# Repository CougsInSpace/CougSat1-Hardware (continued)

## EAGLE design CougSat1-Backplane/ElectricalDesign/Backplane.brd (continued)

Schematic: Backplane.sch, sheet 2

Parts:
J0, J1, J2, J3: CougSat Socket; PCIE-8

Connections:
BUS_I2C0_IRQ: J0.A45 (BUS_I2C0_IRQ), J0.B45 (BUS_I2C0_IRQ), J1.A45 (BUS_I2C0_IRQ), J1.B45 (BUS_I2C0_IRQ), J2.A45 (BUS_I2C0_IRQ), J2.B45 (BUS_I2C0_IRQ), J3.A45 (BUS_I2C0_IRQ), J3.B45 (BUS_I2C0_IRQ); also elsewhere on the board
BUS_I2C0_SCL: J0.A44 (BUS_I2C0_SCL), J0.B44 (BUS_I2C0_SCL), J1.A44 (BUS_I2C0_SCL), J1.B44 (BUS_I2C0_SCL), J2.A44 (BUS_I2C0_SCL), J2.B44 (BUS_I2C0_SCL), J3.A44 (BUS_I2C0_SCL), J3.B44 (BUS_I2C0_SCL); also elsewhere on the board
BUS_I2C0_SDA: J0.A43 (BUS_I2C0_SDA), J0.B43 (BUS_I2C0_SDA), J1.A43 (BUS_I2C0_SDA), J1.B43 (BUS_I2C0_SDA), J2.A43 (BUS_I2C0_SDA), J2.B43 (BUS_I2C0_SDA), J3.A43 (BUS_I2C0_SDA), J3.B43 (BUS_I2C0_SDA); also elsewhere on the board
BUS_I2C1_IRQ: J0.A32 (BUS_I2C1_IRQ), J0.B32 (BUS_I2C1_IRQ), J1.A32 (BUS_I2C1_IRQ), J1.B32 (BUS_I2C1_IRQ), J2.A32 (BUS_I2C1_IRQ), J2.B32 (BUS_I2C1_IRQ), J3.A32 (BUS_I2C1_IRQ), J3.B32 (BUS_I2C1_IRQ); also elsewhere on the board
BUS_I2C1_SCL: J0.A31 (BUS_I2C1_SCL), J0.B31 (BUS_I2C1_SCL), J1.A31 (BUS_I2C1_SCL), J1.B31 (BUS_I2C1_SCL), J2.A31 (BUS_I2C1_SCL), J2.B31 (BUS_I2C1_SCL), J3.A31 (BUS_I2C1_SCL), J3.B31 (BUS_I2C1_SCL); also elsewhere on the board
BUS_I2C1_SDA: J0.A30 (BUS_I2C1_SDA), J0.B30 (BUS_I2C1_SDA), J1.A30 (BUS_I2C1_SDA), J1.B30 (BUS_I2C1_SDA), J2.A30 (BUS_I2C1_SDA), J2.B30 (BUS_I2C1_SDA), J3.A30 (BUS_I2C1_SDA), J3.B30 (BUS_I2C1_SDA); also elsewhere on the board
BUS_JTAG_EN-0: J0.B46 (BUS_JTAG_EN-0), J1.B46 (BUS_JTAG_EN-0), J2.B46 (BUS_JTAG_EN-0), J3.B46 (BUS_JTAG_EN-0); also elsewhere on the board
BUS_JTAG_EN-1: J0.B47 (BUS_JTAG_EN-1), J1.B47 (BUS_JTAG_EN-1), J2.B47 (BUS_JTAG_EN-1), J3.B47 (BUS_JTAG_EN-1); also elsewhere on the board
BUS_JTAG_EN-2: J0.B48 (BUS_JTAG_EN-2), J1.B48 (BUS_JTAG_EN-2), J2.B48 (BUS_JTAG_EN-2), J3.B48 (BUS_JTAG_EN-2); also elsewhere on the board
BUS_JTAG_EN-3: J0.B49 (BUS_JTAG_EN-3), J1.B49 (BUS_JTAG_EN-3), J2.B49 (BUS_JTAG_EN-3), J3.B49 (BUS_JTAG_EN-3); also elsewhere on the board
BUS_JTAG_TCK: J0.A46 (BUS_JTAG_TCK), J1.A46 (BUS_JTAG_TCK), J2.A46 (BUS_JTAG_TCK), J3.A46 (BUS_JTAG_TCK); also elsewhere on the board
BUS_JTAG_TDI: J0.A47 (BUS_JTAG_TDI), J1.A47 (BUS_JTAG_TDI), J2.A47 (BUS_JTAG_TDI), J3.A47 (BUS_JTAG_TDI); also elsewhere on the board
BUS_JTAG_TDO: J0.A48 (BUS_JTAG_TDO), J1.A48 (BUS_JTAG_TDO), J2.A48 (BUS_JTAG_TDO), J3.A48 (BUS_JTAG_TDO); also elsewhere on the board
BUS_JTAG_TMS: J0.A49 (BUS_JTAG_TMS), J1.A49 (BUS_JTAG_TMS), J2.A49 (BUS_JTAG_TMS), J3.A49 (BUS_JTAG_TMS); also elsewhere on the board
BUS_SPI_MISO: J0.A38 (BUS_SPI_MISO), J0.B38 (BUS_SPI_MISO), J1.A38 (BUS_SPI_MISO), J1.B38 (BUS_SPI_MISO), J2.A38 (BUS_SPI_MISO), J2.B38 (BUS_SPI_MISO), J3.A38 (BUS_SPI_MISO), J3.B38 (BUS_SPI_MISO); also elsewhere on the board
BUS_SPI_MOSI: J0.A39 (BUS_SPI_MOSI), J0.B39 (BUS_SPI_MOSI), J1.A39 (BUS_SPI_MOSI), J1.B39 (BUS_SPI_MOSI), J2.A39 (BUS_SPI_MOSI), J2.B39 (BUS_SPI_MOSI), J3.A39 (BUS_SPI_MOSI), J3.B39 (BUS_SPI_MOSI); also elsewhere on the board
BUS_SPI_SCK: J0.A37 (BUS_SPI_SCK), J0.B37 (BUS_SPI_SCK), J1.A37 (BUS_SPI_SCK), J1.B37 (BUS_SPI_SCK), J2.A37 (BUS_SPI_SCK), J2.B37 (BUS_SPI_SCK), J3.A37 (BUS_SPI_SCK), J3.B37 (BUS_SPI_SCK); also elsewhere on the board
COM_SPI_CS: J0.A36 (COM_SPI_CS), J0.B36 (COM_SPI_CS), J1.A36 (COM_SPI_CS), J1.B36 (COM_SPI_CS), J2.A36 (COM_SPI_CS), J2.B36 (COM_SPI_CS), J3.A36 (COM_SPI_CS), J3.B36 (COM_SPI_CS); also elsewhere on the board
COM_SPI_MISO: J0.A34 (COM_SPI_MISO), J0.B34 (COM_SPI_MISO), J1.A34 (COM_SPI_MISO), J1.B34 (COM_SPI_MISO), J2.A34 (COM_SPI_MISO), J2.B34 (COM_SPI_MISO), J3.A34 (COM_SPI_MISO), J3.B34 (COM_SPI_MISO); also elsewhere on the board
COM_SPI_MOSI: J0.A35 (COM_SPI_MOSI), J0.B35 (COM_SPI_MOSI), J1.A35 (COM_SPI_MOSI), J1.B35 (COM_SPI_MOSI), J2.A35 (COM_SPI_MOSI), J2.B35 (COM_SPI_MOSI), J3.A35 (COM_SPI_MOSI), J3.B35 (COM_SPI_MOSI); also elsewhere on the board
COM_SPI_SCK: J0.A33 (COM_SPI_SCK), J0.B33 (COM_SPI_SCK), J1.A33 (COM_SPI_SCK), J1.B33 (COM_SPI_SCK), J2.A33 (COM_SPI_SCK), J2.B33 (COM_SPI_SCK), J3.A33 (COM_SPI_SCK), J3.B33 (COM_SPI_SCK); also elsewhere on the board
CTRL_SYNC: J0.A42 (CTRL_SYNC), J0.B42 (CTRL_SYNC), J1.A42 (CTRL_SYNC), J1.B42 (CTRL_SYNC), J2.A42 (CTRL_SYNC), J2.B42 (CTRL_SYNC), J3.A42 (CTRL_SYNC), J3.B42 (CTRL_SYNC); also elsewhere on the board
GPIO-0: J0.A24 (GPIO-0), J1.A24 (GPIO-0), J2.A24 (GPIO-0), J3.A24 (GPIO-0); also elsewhere on the board
GPIO-1: J0.A25 (GPIO-1), J1.A25 (GPIO-1), J2.A25 (GPIO-1), J3.A25 (GPIO-1); also elsewhere on the board
GPIO-2: J0.A26 (GPIO-2), J1.A26 (GPIO-2), J2.A26 (GPIO-2), J3.A26 (GPIO-2); also elsewhere on the board
GPIO-3: J0.A27 (GPIO-3), J1.A27 (GPIO-3), J2.A27 (GPIO-3), J3.A27 (GPIO-3); also elsewhere on the board
GPIO-4: J0.A28 (GPIO-4), J1.A28 (GPIO-4), J2.A28 (GPIO-4), J3.A28 (GPIO-4); also elsewhere on the board
GPIO-5: J0.A29 (GPIO-5), J1.A29 (GPIO-5), J2.A29 (GPIO-5), J3.A29 (GPIO-5); also elsewhere on the board
GPIO-6: J0.A41 (GPIO-6), J1.A41 (GPIO-6), J2.A41 (GPIO-6), J3.A41 (GPIO-6); also elsewhere on the board
GPIO-7: J0.B41 (GPIO-7), J1.B41 (GPIO-7), J2.B41 (GPIO-7), J3.B41 (GPIO-7); also elsewhere on the board

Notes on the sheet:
<3A4>
<3B4>
<3C4>

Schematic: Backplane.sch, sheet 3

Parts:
J4: CougSat Socket; PCIE-8

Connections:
BUS_I2C0_IRQ: J4.A45 (BUS_I2C0_IRQ), J4.B45 (BUS_I2C0_IRQ); also elsewhere on the board
BUS_I2C0_SCL: J4.A44 (BUS_I2C0_SCL), J4.B44 (BUS_I2C0_SCL); also elsewhere on the board
BUS_I2C0_SDA: J4.A43 (BUS_I2C0_SDA), J4.B43 (BUS_I2C0_SDA); also elsewhere on the board
BUS_I2C1_IRQ: J4.A32 (BUS_I2C1_IRQ), J4.B32 (BUS_I2C1_IRQ); also elsewhere on the board
BUS_I2C1_SCL: J4.A31 (BUS_I2C1_SCL), J4.B31 (BUS_I2C1_SCL); also elsewhere on the board
BUS_I2C1_SDA: J4.A30 (BUS_I2C1_SDA), J4.B30 (BUS_I2C1_SDA); also elsewhere on the board
BUS_JTAG_EN-0: J4.B46 (BUS_JTAG_EN-0); also elsewhere on the board
BUS_JTAG_EN-1: J4.B47 (BUS_JTAG_EN-1); also elsewhere on the board
BUS_JTAG_EN-2: J4.B48 (BUS_JTAG_EN-2); also elsewhere on the board
BUS_JTAG_EN-3: J4.B49 (BUS_JTAG_EN-3); also elsewhere on the board
BUS_JTAG_TCK: J4.A46 (BUS_JTAG_TCK); also elsewhere on the board
BUS_JTAG_TDI: J4.A47 (BUS_JTAG_TDI); also elsewhere on the board
BUS_JTAG_TDO: J4.A48 (BUS_JTAG_TDO); also elsewhere on the board
BUS_JTAG_TMS: J4.A49 (BUS_JTAG_TMS); also elsewhere on the board
BUS_SPI_MISO: J4.A38 (BUS_SPI_MISO), J4.B38 (BUS_SPI_MISO); also elsewhere on the board
BUS_SPI_MOSI: J4.A39 (BUS_SPI_MOSI), J4.B39 (BUS_SPI_MOSI); also elsewhere on the board
BUS_SPI_SCK: J4.A37 (BUS_SPI_SCK), J4.B37 (BUS_SPI_SCK); also elsewhere on the board
COM_SPI_CS: J4.A36 (COM_SPI_CS), J4.B36 (COM_SPI_CS); also elsewhere on the board
COM_SPI_MISO: J4.A34 (COM_SPI_MISO), J4.B34 (COM_SPI_MISO); also elsewhere on the board
COM_SPI_MOSI: J4.A35 (COM_SPI_MOSI), J4.B35 (COM_SPI_MOSI); also elsewhere on the board
COM_SPI_SCK: J4.A33 (COM_SPI_SCK), J4.B33 (COM_SPI_SCK); also elsewhere on the board
CTRL_SYNC: J4.A42 (CTRL_SYNC), J4.B42 (CTRL_SYNC); also elsewhere on the board
GPIO-0: J4.A24 (GPIO-0); also elsewhere on the board
GPIO-1: J4.A25 (GPIO-1); also elsewhere on the board
GPIO-2: J4.A26 (GPIO-2); also elsewhere on the board
GPIO-3: J4.A27 (GPIO-3); also elsewhere on the board
GPIO-4: J4.A28 (GPIO-4); also elsewhere on the board
GPIO-5: J4.A29 (GPIO-5); also elsewhere on the board
GPIO-6: J4.A41 (GPIO-6); also elsewhere on the board
GPIO-7: J4.B41 (GPIO-7); also elsewhere on the board

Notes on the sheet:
<2A6>
<2B6>
<2C6>

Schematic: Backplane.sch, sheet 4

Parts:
J0, J1, J2, J3, J4: CougSat Socket; PCIE-8

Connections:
PGND: J0.A21 (PGND), J0.A22 (PGND), J0.A23 (PGND), J0.B21 (PGND), J0.B22 (PGND), J0.B23 (PGND), J0.B24 (PGND), J0.B25 (PGND), J0.B26 (PGND), J0.B27 (PGND), J0.B28 (PGND), J0.B29 (PGND), J1.A21 (PGND), J1.A22 (PGND), J1.A23 (PGND), J1.B21 (PGND), J1.B22 (PGND), J1.B23 (PGND), J1.B24 (PGND), J1.B25 (PGND), J1.B26 (PGND), J1.B27 (PGND), J1.B28 (PGND), J1.B29 (PGND), J2.A21 (PGND), J2.A22 (PGND), J2.A23 (PGND), J2.B21 (PGND), J2.B22 (PGND), J2.B23 (PGND), J2.B24 (PGND), J2.B25 (PGND), J2.B26 (PGND), J2.B27 (PGND), J2.B28 (PGND), J2.B29 (PGND), J3.A21 (PGND), J3.A22 (PGND), J3.A23 (PGND), J3.B21 (PGND), J3.B22 (PGND), J3.B23 (PGND), J3.B24 (PGND), J3.B25 (PGND), J3.B26 (PGND), J3.B27 (PGND), J3.B28 (PGND), J3.B29 (PGND), J4.A21 (PGND), J4.A22 (PGND), J4.A23 (PGND), J4.B21 (PGND), J4.B22 (PGND), J4.B23 (PGND), J4.B24 (PGND), J4.B25 (PGND), J4.B26 (PGND), J4.B27 (PGND), J4.B28 (PGND), J4.B29 (PGND); also elsewhere on the board
PR_3.3V-0: J0.A1 (PR_3.3V-0), J0.B1 (PR_3.3V-0), J1.A1 (PR_3.3V-0), J1.B1 (PR_3.3V-0), J2.A1 (PR_3.3V-0), J2.B1 (PR_3.3V-0), J3.A1 (PR_3.3V-0), J3.B1 (PR_3.3V-0), J4.A1 (PR_3.3V-0), J4.B1 (PR_3.3V-0)
PR_3.3V-1: J0.A2 (PR_3.3V-1), J0.B2 (PR_3.3V-1), J1.A2 (PR_3.3V-1), J1.B2 (PR_3.3V-1), J2.A2 (PR_3.3V-1), J2.B2 (PR_3.3V-1), J3.A2 (PR_3.3V-1), J3.B2 (PR_3.3V-1), J4.A2 (PR_3.3V-1), J4.B2 (PR_3.3V-1)
PR_3.3V-2: J0.A3 (PR_3.3V-2), J0.B3 (PR_3.3V-2), J1.A3 (PR_3.3V-2), J1.B3 (PR_3.3V-2), J2.A3 (PR_3.3V-2), J2.B3 (PR_3.3V-2), J3.A3 (PR_3.3V-2), J3.B3 (PR_3.3V-2), J4.A3 (PR_3.3V-2), J4.B3 (PR_3.3V-2)
PR_3.3V-3: J0.A4 (PR_3.3V-3), J0.B4 (PR_3.3V-3), J1.A4 (PR_3.3V-3), J1.B4 (PR_3.3V-3), J2.A4 (PR_3.3V-3), J2.B4 (PR_3.3V-3), J3.A4 (PR_3.3V-3), J3.B4 (PR_3.3V-3), J4.A4 (PR_3.3V-3), J4.B4 (PR_3.3V-3)
PR_3.3V-4: J0.A5 (PR_3.3V-4), J0.B5 (PR_3.3V-4), J1.A5 (PR_3.3V-4), J1.B5 (PR_3.3V-4), J2.A5 (PR_3.3V-4), J2.B5 (PR_3.3V-4), J3.A5 (PR_3.3V-4), J3.B5 (PR_3.3V-4), J4.A5 (PR_3.3V-4), J4.B5 (PR_3.3V-4)
PR_3.3V-5: J0.A6 (PR_3.3V-5), J0.B6 (PR_3.3V-5), J1.A6 (PR_3.3V-5), J1.B6 (PR_3.3V-5), J2.A6 (PR_3.3V-5), J2.B6 (PR_3.3V-5), J3.A6 (PR_3.3V-5), J3.B6 (PR_3.3V-5), J4.A6 (PR_3.3V-5), J4.B6 (PR_3.3V-5)
PR_3.3V-6: J0.A7 (PR_3.3V-6), J0.B7 (PR_3.3V-6), J1.A7 (PR_3.3V-6), J1.B7 (PR_3.3V-6), J2.A7 (PR_3.3V-6), J2.B7 (PR_3.3V-6), J3.A7 (PR_3.3V-6), J3.B7 (PR_3.3V-6), J4.A7 (PR_3.3V-6), J4.B7 (PR_3.3V-6)
PR_3.3V-7: J0.A8 (PR_3.3V-7), J0.B8 (PR_3.3V-7), J1.A8 (PR_3.3V-7), J1.B8 (PR_3.3V-7), J2.A8 (PR_3.3V-7), J2.B8 (PR_3.3V-7), J3.A8 (PR_3.3V-7), J3.B8 (PR_3.3V-7), J4.A8 (PR_3.3V-7), J4.B8 (PR_3.3V-7)
PR_3.3V-8: J0.A9 (PR_3.3V-8), J0.B9 (PR_3.3V-8), J1.A9 (PR_3.3V-8), J1.B9 (PR_3.3V-8), J2.A9 (PR_3.3V-8), J2.B9 (PR_3.3V-8), J3.A9 (PR_3.3V-8), J3.B9 (PR_3.3V-8), J4.A9 (PR_3.3V-8), J4.B9 (PR_3.3V-8)
PR_3.3V-9: J0.A10 (PR_3.3V-9), J0.B10 (PR_3.3V-9), J1.A10 (PR_3.3V-9), J1.B10 (PR_3.3V-9), J2.A10 (PR_3.3V-9), J2.B10 (PR_3.3V-9), J3.A10 (PR_3.3V-9), J3.B10 (PR_3.3V-9), J4.A10 (PR_3.3V-9), J4.B10 (PR_3.3V-9)
PR_3.3V-10: J0.A11 (PR_3.3V-10), J0.B11 (PR_3.3V-10), J1.A11 (PR_3.3V-10), J1.B11 (PR_3.3V-10), J2.A11 (PR_3.3V-10), J2.B11 (PR_3.3V-10), J3.A11 (PR_3.3V-10), J3.B11 (PR_3.3V-10), J4.A11 (PR_3.3V-10), J4.B11 (PR_3.3V-10)
PR_3.3V-11: J0.A12 (PR_3.3V-11), J0.B12 (PR_3.3V-11), J1.A12 (PR_3.3V-11), J1.B12 (PR_3.3V-11), J2.A12 (PR_3.3V-11), J2.B12 (PR_3.3V-11), J3.A12 (PR_3.3V-11), J3.B12 (PR_3.3V-11), J4.A12 (PR_3.3V-11), J4.B12 (PR_3.3V-11)
PR_3.3V-12: J0.A13 (PR_3.3V-12), J0.B13 (PR_3.3V-12), J1.A13 (PR_3.3V-12), J1.B13 (PR_3.3V-12), J2.A13 (PR_3.3V-12), J2.B13 (PR_3.3V-12), J3.A13 (PR_3.3V-12), J3.B13 (PR_3.3V-12), J4.A13 (PR_3.3V-12), J4.B13 (PR_3.3V-12)
PR_BATT-0: J0.A14 (PR_BATT-0), J0.B14 (PR_BATT-0), J1.A14 (PR_BATT-0), J1.B14 (PR_BATT-0), J2.A14 (PR_BATT-0), J2.B14 (PR_BATT-0), J3.A14 (PR_BATT-0), J3.B14 (PR_BATT-0), J4.A14 (PR_BATT-0), J4.B14 (PR_BATT-0)
PR_BATT-1: J0.A15 (PR_BATT-1), J0.B15 (PR_BATT-1), J1.A15 (PR_BATT-1), J1.B15 (PR_BATT-1), J2.A15 (PR_BATT-1), J2.B15 (PR_BATT-1), J3.A15 (PR_BATT-1), J3.B15 (PR_BATT-1), J4.A15 (PR_BATT-1), J4.B15 (PR_BATT-1)
PR_BATT-2: J0.A16 (PR_BATT-2), J0.B16 (PR_BATT-2), J1.A16 (PR_BATT-2), J1.B16 (PR_BATT-2), J2.A16 (PR_BATT-2), J2.B16 (PR_BATT-2), J3.A16 (PR_BATT-2), J3.B16 (PR_BATT-2), J4.A16 (PR_BATT-2), J4.B16 (PR_BATT-2)
PR_BATT-3: J0.A17 (PR_BATT-3), J0.B17 (PR_BATT-3), J1.A17 (PR_BATT-3), J1.B17 (PR_BATT-3), J2.A17 (PR_BATT-3), J2.B17 (PR_BATT-3), J3.A17 (PR_BATT-3), J3.B17 (PR_BATT-3), J4.A17 (PR_BATT-3), J4.B17 (PR_BATT-3)
PR_BATT-4: J0.A18 (PR_BATT-4), J0.B18 (PR_BATT-4), J1.A18 (PR_BATT-4), J1.B18 (PR_BATT-4), J2.A18 (PR_BATT-4), J2.B18 (PR_BATT-4), J3.A18 (PR_BATT-4), J3.B18 (PR_BATT-4), J4.A18 (PR_BATT-4), J4.B18 (PR_BATT-4)
PR_BATT-5: J0.A19 (PR_BATT-5), J0.B19 (PR_BATT-5), J1.A19 (PR_BATT-5), J1.B19 (PR_BATT-5), J2.A19 (PR_BATT-5), J2.B19 (PR_BATT-5), J3.A19 (PR_BATT-5), J3.B19 (PR_BATT-5), J4.A19 (PR_BATT-5), J4.B19 (PR_BATT-5)
PR_BATT-6: J0.A20 (PR_BATT-6), J0.B20 (PR_BATT-6), J1.A20 (PR_BATT-6), J1.B20 (PR_BATT-6), J2.A20 (PR_BATT-6), J2.B20 (PR_BATT-6), J3.A20 (PR_BATT-6), J3.B20 (PR_BATT-6), J4.A20 (PR_BATT-6), J4.B20 (PR_BATT-6)
PWR_CTRL_SW: J0.A40 (PWR_CTRL_SW), J0.B40 (PWR_CTRL_SW), J1.A40 (PWR_CTRL_SW), J1.B40 (PWR_CTRL_SW), J2.A40 (PWR_CTRL_SW), J2.B40 (PWR_CTRL_SW), J3.A40 (PWR_CTRL_SW), J3.B40 (PWR_CTRL_SW), J4.A40 (PWR_CTRL_SW), J4.B40 (PWR_CTRL_SW)

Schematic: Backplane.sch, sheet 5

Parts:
C1, C2: 100nF 10%; 1608
H1, H2: M3; MOUNTING_HOLE-3.3
LOGO2: SIGNATUREHENDRIK; SIGN-HENDRIK
R1, R2: 0Ω <20mΩ; 1608

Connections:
CHASSIS1: C1.1, H1.1, H1.V1, H1.V2, H1.V3, H1.V4, H1.V5, H1.V6, H1.V7, H1.V8, H1.V9, H1.V10, R1.2
CHASSIS2: C2.1, H2.1, H2.V1, H2.V2, H2.V3, H2.V4, H2.V5, H2.V6, H2.V7, H2.V8, H2.V9, H2.V10, R2.2
PGND: C1.2, C2.2, R1.1, R2.1; also elsewhere on the board

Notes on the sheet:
CAD Note: Mounting Holes
Slot 0
Slot 1
Slot 2
Slot 3
Slot 4

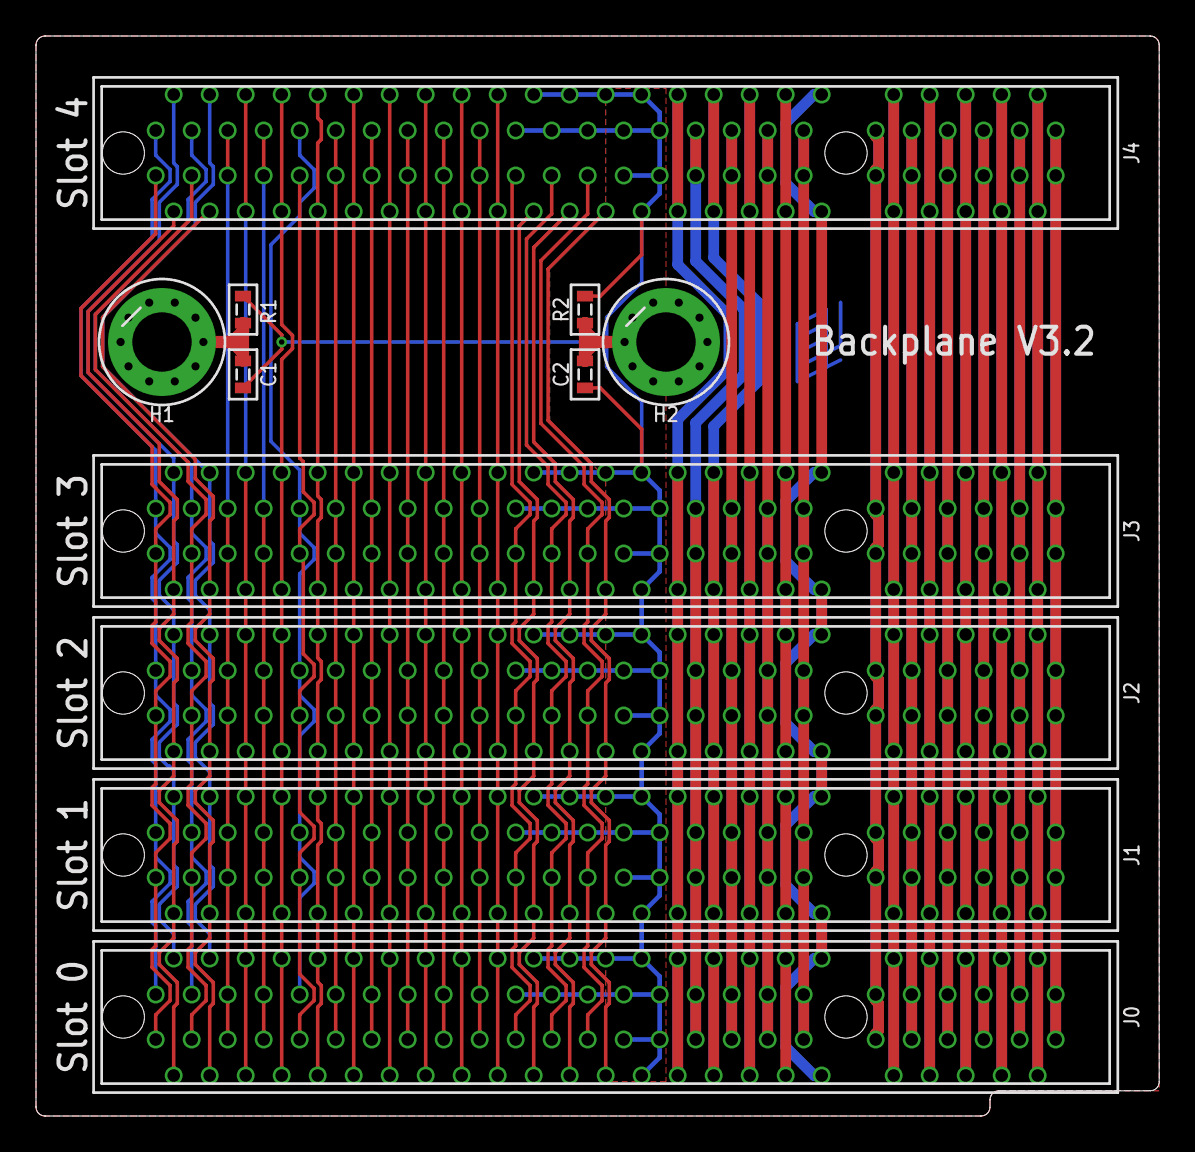
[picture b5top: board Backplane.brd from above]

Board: 2 copper layers, 62.4 x 60.0 mm, 12 parts (1 on the bottom side), 54 nets.

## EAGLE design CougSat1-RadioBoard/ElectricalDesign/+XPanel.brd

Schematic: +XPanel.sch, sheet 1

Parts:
LOGO1: SIGNATUREJAYSON; SIGN-JAYSON

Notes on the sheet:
Page 1: Block Diagram Page 2: Photodiode & ADC Page 3: Antennae Page 4: Mechanical
Low Gain 700mm Antenna
GPS Patch Antenna
Antenna Deploy Release
Connector: To Comms
Connector: To EPS
Connector: GPS to ADCS
Power
Photodiode
ADC
Connector: To ADCS
I²C
Page 2
Page 3
Thermistors
Variant:

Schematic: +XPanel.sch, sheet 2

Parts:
C1, C5, C6, C8: 100nF 10%; 1608
C2: 1µF 10%; 1608
C3: 10µF 10%; 1608
C7: 4.7µF 10%; 4028-POL
D1: SFH 2430; SFH2430
FB1: 1.5kΩ @ 100MHz; 1608
J4: ADCS Connector; PICOLOCK1.5-04
R2, R3, R4, R5, R10: 0Ω <20mΩ; 1608
R6: 1kΩ 0.1%; 1608
R7: 2kΩ 0.1%; 1608
R16, R17: 10kΩ 0.1%; 1608
RN1: 10kΩ 5%; 3264
RT1, RT2, RT3, RT4, RT5, RT6, RT7: 10kΩ 5%; 1608
TP1, TP2: TEST_POINT-SMD-C-1.25; SMD-C-1.25
U1: AD7291; QFN-20-4040
U2: AD8515; SOT23-5

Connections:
3.3V: C5.1, D1.C, FB1.1, J4.3, R2.2, R3.2, R6.2, R16.2, R17.2, U1.16 (VDRIVE)
ADC_AS0: R2.1, R4.2, U1.11 (AS0)
ADC_AS1: R3.1, R5.2, U1.13 (AS1)
AGND: C1.2, C2.2, C3.2, C6.2, C7.C, C8.2, R7.1, R10.1, RT1.1, RT2.1, RT3.1, RT4.1, RT5.1, RT6.1, RT7.1, U1.6 (AGND), U2.2 (V-)
AVDD: C1.1, C6.1, C7.A, C8.1, FB1.2, TP2.1, U1.10 (VDD), U2.5 (V+)
AVREF: RN1.5 (C), RN1.10 (C), U2.1 (OUT), U2.4 (IN-)
AVREF_UNBUF: C3.1, TP1.1, U1.7 (VREF), U2.3 (IN+)
DCAP: C2.1, U1.8 (DCAP)
DGND: C5.2, J4.4, R4.1, R5.1, R10.2, U1.9 (DGND), U1.PAD (DGND)
I2C_SCL_ADCS: J4.2, R16.1, U1.15 (SCL)
I2C_SDA_ADCS: J4.1, R17.1, U1.14 (SDA)
PD_RST: R6.1, U1.17 (!PD!/!RST)
PHOTO: D1.A, R7.2, U1.18 (IN0)
THERM-0: RN1.6 (5), RT3.2, U1.19 (IN1)
THERM-1: RN1.7 (6), RT4.2, U1.20 (IN2)
THERM-2: RN1.8 (7), RT7.2, U1.1 (IN3)
THERM-3: RN1.4, RT6.2, U1.2 (IN4)
THERM-4: RN1.3, RT1.2, U1.3 (IN5)
THERM-5: RN1.2, RT5.2, U1.4 (IN6)
THERM-6: RN1.1, RT2.2, U1.5 (IN7)

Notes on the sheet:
CAD Note: Place facing outwards in the center of the board
<2A3
2C6>
2C5>
2C5>
2C4>
2C4>
Addr = 0x40|R/!W
CAD Note: Decoupling (AD8515 Pin 5)
CAD Note: Decoupling for AD7291 (C3 for Pin 10, C13 for Pin 16)
2B1>
2A2>

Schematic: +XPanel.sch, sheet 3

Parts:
AE1: GPS Antenna; ANTENNA-GPS
C4, C9, C10, C11, C12, C13: 100nF 10%; 1608
H1, H2, H6, H7, H11, H12: M3; MOUNTING_HOLE-3.3
H3, H4, H5, H8: M2; MOUNTING_HOLE-2.2
H9, H10: M2 Nut - 1mm; MOUNTING_HOLE-M2_NUT
J1: EPS Connector; PICOLOCK1.5-04
J2: GPS Coax; U.FL
J3: Low Gain Coax; U.FL
J5: Low Gain +; THT-0.7
J6: Low Gain -; THT-0.7
R1, R11, R12, R13, R14, R15: 0Ω <20mΩ; 1608
R8, R9: 5Ω 1%; THT-15MM
Z1: Balun 1:1; CD542

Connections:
CHASSIS: C4.1, C9.1, C10.1, C11.1, C12.1, C13.1, H1.1, H1.V1, H1.V2, H1.V3, H1.V4, H1.V5, H1.V6, H1.V7, H1.V8, H1.V9, H1.V10, H2.1, H2.V1, H2.V2, H2.V3, H2.V4, H2.V5, H2.V6, H2.V7, H2.V8, H2.V9, H2.V10, H6.1, H6.V1, H6.V2, H6.V3, H6.V4, H6.V5, H6.V6, H6.V7, H6.V8, H6.V9, H6.V10, H7.1, H7.V1, H7.V2, H7.V3, H7.V4, H7.V5, H7.V6, H7.V7, H7.V8, H7.V9, H7.V10, H11.1, H11.V1, H11.V2, H11.V3, H11.V4, H11.V5, H11.V6, H11.V7, H11.V8, H11.V9, H11.V10, H12.1, H12.V1, H12.V2, H12.V3, H12.V4, H12.V5, H12.V6, H12.V7, H12.V8, H12.V9, H12.V10, R1.2, R11.2, R12.2, R13.2, R14.2, R15.2
DEPLOYABLE: J1.1, J1.2, R8.2, R9.2
GPS_COAX: AE1.CENTER, J2.CENTER
LOW_GAIN_COAX: J3.CENTER, Z1.6 (SECONDARY-DOT)
LOW_GAIN_N: J6.1, Z1.3 (PRIMARY)
LOW_GAIN_P: J5.1, Z1.1 (PRIMARY-DOT)
PGND: C4.2, C9.2, C10.2, C11.2, C12.2, C13.2, H4.1, H4.V1, H4.V2, H4.V3, H4.V4, H4.V5, H4.V6, H4.V7, H4.V8, H5.1, H5.V1, H5.V2, H5.V3, H5.V4, H5.V5, H5.V6, H5.V7, H5.V8, J1.4, R1.1, R8.1, R9.1, R11.1, R12.1, R13.1, R14.1, R15.1
RFGND-0: H9.1, H9.V1, H9.V2, H9.V3, H9.V4, H9.V5, H9.V6, H9.V7, H9.V8, H10.1, H10.V1, H10.V2, H10.V3, H10.V4, H10.V5, H10.V6, H10.V7, H10.V8, J3.SHIELD@1 (SHIELD), J3.SHIELD@2 (SHIELD), J3.SHIELD@13 (SHIELD), Z1.4 (SECONDARY)
RFGND-1: AE1.GND (SHIELD), J2.SHIELD@1 (SHIELD), J2.SHIELD@2 (SHIELD), J2.SHIELD@13 (SHIELD)
SENSE: H3.1, H3.V1, H3.V2, H3.V3, H3.V4, H3.V5, H3.V6, H3.V7, H3.V8, H8.1, H8.V1, H8.V2, H8.V3, H8.V4, H8.V5, H8.V6, H8.V7, H8.V8, J1.3

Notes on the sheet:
Note: The low gain antenna wraps around posts in these holes which shorts them together. When deployed, the deploy sense pin will be pulled high by the EPS

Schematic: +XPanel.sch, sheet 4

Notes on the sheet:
ADCS Picolock Connector
EPS Picolock Connector
Low Gain Coax
GPS Coax

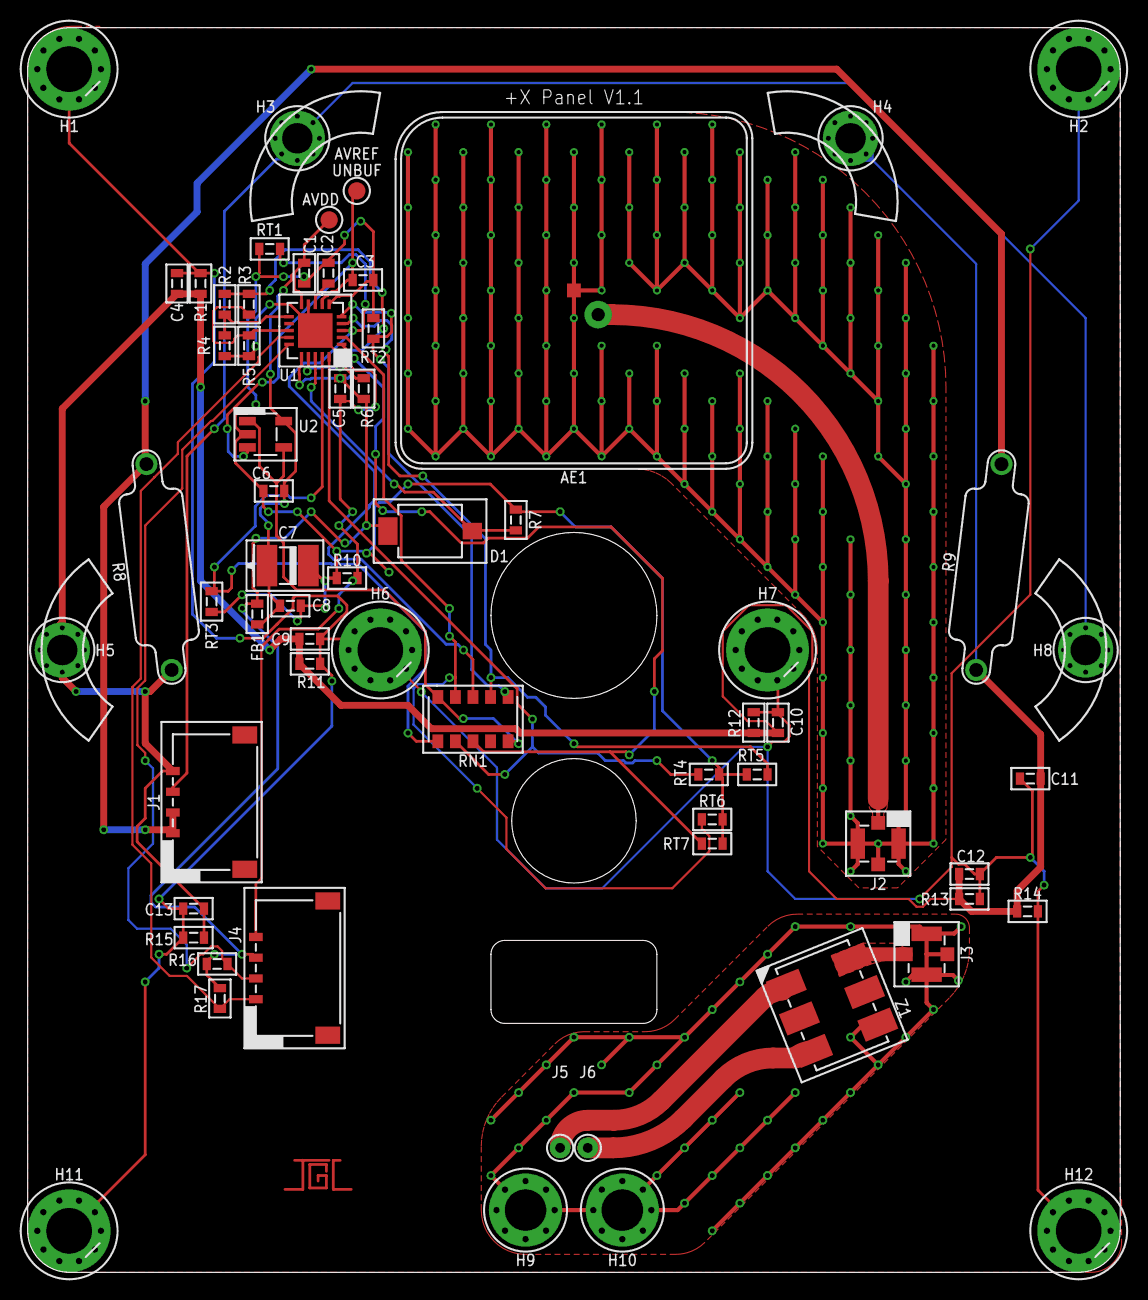
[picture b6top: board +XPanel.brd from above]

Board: 2 copper layers, 79.0 x 90.0 mm, 65 parts (0 on the bottom side), 30 nets.

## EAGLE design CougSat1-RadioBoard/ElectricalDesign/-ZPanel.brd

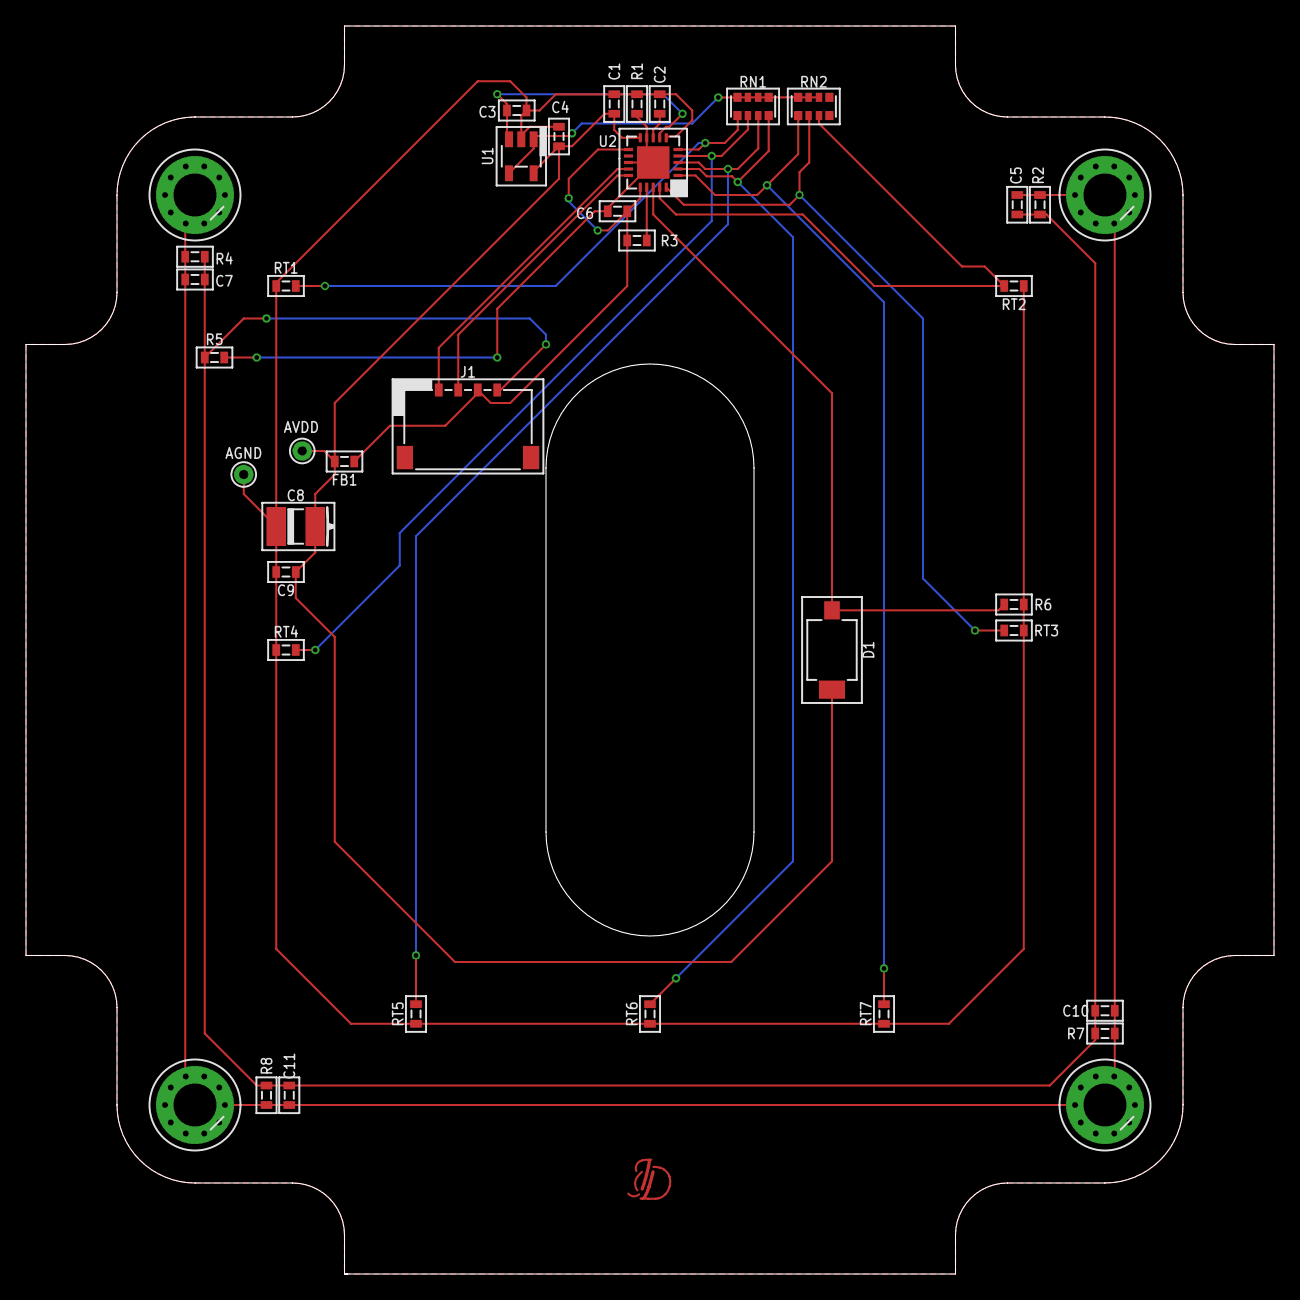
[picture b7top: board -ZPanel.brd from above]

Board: 2 copper layers, 96.0 x 96.0 mm, 40 parts (0 on the bottom side), 20 nets.

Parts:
C1, C4, C5, C6, C7, C9, C10, C11: 100nF 10%; 1608
C2: 1µF 10%; 1608
C3: 10µF 10%; 1608
C8: 4.7µF 10%; 4028-POL
D1: SFH 2430; SFH2430
FB1: 1.5kΩ @ 100MHz; 1608
H1, H2, H3, H4: M3; MOUNTING_HOLE-3.3
J1: ADCS; PICOLOCK1.5-04
LOGO1: SIGNATUREJOSH; SIGN-JOSH
R1, R2, R4, R5, R7, R8: 0Ω <20mΩ; 1608
R3: 1kΩ 0.1%; 1608
R6: 150Ω 1%; 1608
RN1, RN2: 10kΩ 1%; 1632
RT1, RT2, RT3, RT4, RT5, RT6, RT7: 10kΩ 5%; 1608
TP1, TP2: TEST_POINT-THT-0.7; THT-0.7
U1: AD8515; SOT23-5
U2: AD7291; QFN-20-4040

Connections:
3.3V: C6.1, FB1.1, J1.3, R3.2, U2.11, U2.16
AGND: C1.2, C2.2, C3.2, C4.2, C8.C, C9.2, R1.1, R6.1, RT1.1, RT2.1, RT3.1, RT4.1, RT5.1, RT6.1, RT7.1, TP2.1, U1.2, U2.6
AVDD: C1.1, C4.1, C8.A, C9.1, D1.C, FB1.2, TP1.1, U1.5, U2.10
AVREF: RN1.5, RN1.6, RN1.7, RN1.8, RN2.6, RN2.7, RN2.8, U1.1, U1.4
BOTTOM_LEFT: RN1.3, RT5.2, U2.3
BOTTOM_MIDDLE: RN1.4, RT6.2, U2.2
BOTTOM_RIGHT: RN2.1, RT7.2, U2.1
CHASSIS: C5.1, C7.1, C10.1, C11.1, H1.1, H1.V1, H1.V2, H1.V3, H1.V4, H1.V5, H1.V6, H1.V7, H1.V8, H1.V9, H1.V10, H2.1, H2.V1, H2.V2, H2.V3, H2.V4, H2.V5, H2.V6, H2.V7, H2.V8, H2.V9, H2.V10, H3.1, H3.V1, H3.V2, H3.V3, H3.V4, H3.V5, H3.V6, H3.V7, H3.V8, H3.V9, H3.V10, H4.1, H4.V1, H4.V2, H4.V3, H4.V4, H4.V5, H4.V6, H4.V7, H4.V8, H4.V9, H4.V10, R2.2, R4.2, R7.2, R8.2
DCAP: C2.1, U2.8
DGND: C6.2, R1.2, R5.2, U2.9, U2.13, U2.PAD
I2C_SCL_ADCS: J1.2, U2.15
I2C_SDA_ADCS: J1.1, U2.14
MIDDLE_LEFT: RN1.2, RT4.2, U2.4
MIDDLE_RIGHT: RN2.2, RT3.2, U2.20
PD/RST: R3.1, U2.17
PGND: C5.2, C7.2, C10.2, C11.2, J1.4, R2.1, R4.1, R5.1, R7.1, R8.1
PHOTODIODE_ADC: D1.A, R6.2, U2.18
TOP_LEFT: RN1.1, RT1.2, U2.5
TOP_RIGHT: RN2.3, RT2.2, U2.19
VREF: C3.1, U1.3, U2.7

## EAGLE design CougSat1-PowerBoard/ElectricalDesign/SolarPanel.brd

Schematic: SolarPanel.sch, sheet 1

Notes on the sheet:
Solar Cell
Battery Charger with MPPT
Connector: To EPS
ADC
4.1V Current Limited
3.3V
I²C
Page 2
Page 3
Page 4
Page 1: Block Diagram Page 2: Solar Cells, MPPT Page 3: Connectors, I²C GPIO, Magnetorquer Page 4: ADCs Page 5: Mechanical
Magnetorquer
Front side
Back side
Connector: To ADCS
Variant:

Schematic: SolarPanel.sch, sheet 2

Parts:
C107, C120: 1nF 10%; 1608
C108, C109, C119, C123: 10µF 10%; 3216
C110, C118: 100nF 10%; 1608
C111, C114, C116, C117: 4.7µF 10%; 3216
C112, C115: 47µF; 4028-POL
D100, D101: SMM4F5.0A; STMITE
L101, L102: 10µH 20%; 6060
PV1, PV2: UTJ; SPECTROLABS-UTJ
R105, R107, R108, R113, R115, R122, R123, R130, R137, R138: 0Ω <20mΩ; 1608
R106, R117, R128, R135: 1kΩ 0.1%; 1608
R114, R129: 820kΩ 1%; 1608
R116, R136: 5mΩ 1%; 1632-KELVIN
R118, R127: 10kΩ 0.1%; 1608
R119, R126: 12mΩ 1%; 3216-KELVIN
R121, R124: 360kΩ 1%; 1608
RT101, RT102: 10kΩ 5%; 1608
U102, U104, U106, U107: INA199C2; SOT363
U103, U105: SPV1040; TSSOP8

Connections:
AGND: R107.1, R107.2, R123.1, R138.1, R138.2, RT101.2, RT102.2, U102.1 (REF), U102.2 (GND), U104.1 (REF), U104.2 (GND), U106.1 (REF), U106.2 (GND), U107.1 (REF), U107.2 (GND); also elsewhere on the board
AVDD: R105.1, R105.2, R108.1, R108.2, U102.3 (VDD), U104.3 (VDD), U106.3 (VDD), U107.3 (VDD); also elsewhere on the board
DGND: R122.1, R123.2; also elsewhere on the board
I_OUT-A: U102.6 (OUT); also elsewhere on the board
I_OUT-B: U107.6 (OUT); also elsewhere on the board
MPPT_FBRES_HIGH-A: R114.2, R115.1
MPPT_FBRES_HIGH-B: R129.2, R137.1
MPPT_FBRES_LOW-A: R113.1, R121.2
MPPT_FBRES_LOW-B: R124.2, R130.1
MPPT_ICTRL-A: R117.1, U103.6 (ICTRL-), U103.7 (ICTRL+)
MPPT_ICTRL-B: R128.1, U105.6 (ICTRL-), U105.7 (ICTRL+)
MPPT_LX-A: L101.2, U103.3 (LX)
MPPT_LX-B: L102.2, U105.3 (LX)
MPPT_OUTCAP-A: C108.2, C109.1
MPPT_OUTCAP-B: C119.1, C123.2
MPPT_SET-A: C110.1, R106.1, R118.1, U103.1 (MPPT-SET)
MPPT_SET-B: C118.1, R127.1, R135.1, U105.1 (MPPT-SET)
MPPT_VCTRL-A: C107.1, R113.2, R114.1, U103.5 (VCTRL)
MPPT_VCTRL-B: C120.1, R129.1, R130.2, U105.5 (VCTRL)
MPPT_VOUT-A: C108.1, D100.C, R116.1, R117.2, U103.4 (VOUT)
MPPT_VOUT-B: C123.1, D101.C, R128.2, R136.1, U105.4 (VOUT)
OUTPUT_CAP-A: C111.2, C114.1
OUTPUT_CAP-B: C116.1, C117.2
PGND: C107.2, C109.2, C110.2, C112.C, C114.2, C115.C, C116.2, C118.2, C119.2, C120.2, D100.A, D101.A, PV1.VSS@1 (A), PV1.VSS@2 (A), PV1.VSS@3 (A), PV2.VSS@1 (A), PV2.VSS@2 (A), PV2.VSS@3 (A), R121.1, R122.2, R124.1, U103.2 (PGND), U105.2 (PGND); also elsewhere on the board
PV_I-A: U104.6 (OUT); also elsewhere on the board
PV_I-B: U106.6 (OUT); also elsewhere on the board
PV_IIN_N-A: C111.1, L101.1, R106.2, R119.2
PV_IIN_N-B: C117.1, L102.1, R126.2, R135.2
PV_I_N-A: R119.2-KELVIN, U104.5 (IN-)
PV_I_N-B: R126.2-KELVIN, U106.5 (IN-)
PV_I_P-A: R119.1-KELVIN, U104.4 (IN+)
PV_I_P-B: R126.1-KELVIN, U106.4 (IN+)
PV_V-A: C112.A, PV2.VCC@1 (C), PV2.VCC@2 (C), PV2.VCC@3 (C), PV2.VCC@4 (C), R119.1; also elsewhere on the board
PV_V-B: C115.A, PV1.VCC@1 (C), PV1.VCC@2 (C), PV1.VCC@3 (C), PV1.VCC@4 (C), R126.1; also elsewhere on the board
TEMP_MPPT-A: RT101.1; also elsewhere on the board
TEMP_MPPT-B: RT102.1; also elsewhere on the board
VOUT-A: R115.2, R116.2; also elsewhere on the board
VOUT-B: R136.2, R137.2; also elsewhere on the board
VOUT_N-A: R116.2-KELVIN, U102.5 (IN-)
VOUT_N-B: R136.2-KELVIN, U107.5 (IN-)
VOUT_P-A: R116.1-KELVIN, U102.4 (IN+)
VOUT_P-B: R136.1-KELVIN, U107.4 (IN+)
X_SHUT-A: R118.2, U103.8 (X_SHUT)
X_SHUT-B: R127.2, U105.8 (X_SHUT)

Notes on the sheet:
Note: Vmax = 1.25V
3C2>
<4A2
CAD Note: Thermally Connected
Variant:
<4A1

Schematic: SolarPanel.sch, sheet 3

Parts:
C100: 100nF 10%; 1608
C101: 4.7µF 10%; 4028-POL
D1: SFH 2430; SFH2430
FB100: 1.5kΩ @ 100MHz; 1608
J100: ADCS; PICOLOCK1.5-04
J101: EPS; PICOLOCK1.5-07
L100: xxx Turns; SMD-3030-2
R3, R4, R5, R7, R8, R102, R143: 10kΩ 0.1%; 1608
R6: 1.2kΩ 0.1%; 1608
R100, R101, R103, R104: 2.2kΩ 1%; 1608
RT1, RT2, RT3, RT4, RT5, RT100, RT103: 10kΩ 5%; 1608
TP100: TEST_POINT-SMD-C-1.25; SMD-C-1.25

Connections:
3.3V: D1.C, FB100.1, J101.1, R100.2, R101.2, R103.2, R104.2; also elsewhere on the board
AGND: C100.2, C101.C, R6.1, RT1.1, RT2.1, RT3.1, RT4.1, RT5.1, RT100.1, RT103.1; also elsewhere on the board
AVDD: C100.1, C101.A, FB100.2, TP100.1; also elsewhere on the board
AVREF-1: R3.2, R4.2, R5.2, R7.2, R8.2, R102.2, R143.2; also elsewhere on the board
I2C_SCL_ADCS: J100.2, R103.1; also elsewhere on the board
I2C_SCL_PMIC: J101.3, R101.1; also elsewhere on the board
I2C_SDA_ADCS: J100.1, R104.1; also elsewhere on the board
I2C_SDA_PMIC: J101.2, R100.1; also elsewhere on the board
MAGNETORQUER-IN: J100.3, L100.1
MAGNETORQUER_OUT: J100.4, L100.2
PGND: J101.6, J101.7; also elsewhere on the board
PHOTODIODE: D1.A, R6.2; also elsewhere on the board
TEMP-0: R5.1, RT3.2; also elsewhere on the board
TEMP-1: R102.1, RT100.2; also elsewhere on the board
TEMP-2: R7.1, RT4.2; also elsewhere on the board
TEMP-3: R3.1, RT1.2; also elsewhere on the board
TEMP-4: R143.1, RT103.2; also elsewhere on the board
TEMP-5: R4.1, RT2.2; also elsewhere on the board
TEMP-6: R8.1, RT5.2; also elsewhere on the board
VOUT-A: J101.5; also elsewhere on the board
VOUT-B: J101.4; also elsewhere on the board

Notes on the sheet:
<4A5>
4A5>
CAD Note: Place at end of bus
Variant:
4C4>
<4C4>
<4C1
4C1>
<2C6
<2A6

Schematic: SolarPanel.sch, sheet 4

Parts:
C102, C126: 10µF 10%; 1608
C103, C104, C105, C106, C122, C124, C125, C127: 100nF 10%; 1608
R109, R110, R111, R112, R131, R132, R133, R134, R141, R142: 0Ω <20mΩ; 1608
R139, R140: 10kΩ 0.1%; 1608
RN100, RN101: 50kΩ 0.1%; 1616
TP101, TP102: TEST_POINT-SMD-C-1.25; SMD-C-1.25
U100, U108: AD7291; QFN-20-4040
U101, U109: AD8515; SOT23-5

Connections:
3.3V: C105.1, C122.1, R109.2, R110.2, R133.2, R134.2, U100.16 (VDRIVE), U100.17 (!PD!/!RST), U108.16 (VDRIVE), U108.17 (!PD!/!RST); also elsewhere on the board
ADC_AS0-ADCS: R110.1, R112.2, U100.11 (AS0)
ADC_AS0-EPS: R132.2, R134.1, U108.11 (AS0)
ADC_AS1-ADCS: R109.1, R111.2, U100.13 (AS1)
ADC_AS1-EPS: R131.2, R133.1, U108.13 (AS1)
ADC_DCAP-ADCS: C103.1, U100.8 (DCAP)
ADC_DCAP-EPS: C124.1, U108.8 (DCAP)
ADC_VREF-ADCS: C102.1, U100.7 (VREF), U101.3 (IN+)
ADC_VREF-EPS: C126.1, U108.7 (VREF), U109.3 (IN+)
AGND: C102.2, C103.2, C104.2, C106.2, C124.2, C125.2, C126.2, C127.2, RN100.1 (A1), RN101.1 (A1), U100.6 (AGND), U101.2 (V-), U108.6 (AGND), U109.2 (V-); also elsewhere on the board
AVDD: C104.1, C106.1, C125.1, C127.1, U100.10 (VDD), U101.5 (V+), U108.10 (VDD), U109.5 (V+); also elsewhere on the board
AVREF-0: R139.2, R140.2, R141.2, TP102.1
AVREF-1: TP101.1, U101.1 (OUT), U101.4 (IN-); also elsewhere on the board
AVREF-BUFF: R141.1, U109.1 (OUT), U109.4 (IN-)
DGND: C105.2, C122.2, R111.1, R112.1, R131.1, R132.1, U100.9 (DGND), U100.PAD (DGND), U108.9 (DGND), U108.PAD (DGND); also elsewhere on the board
I2C_SCL_ADCS: U100.15 (SCL); also elsewhere on the board
I2C_SCL_PMIC: U108.15 (SCL); also elsewhere on the board
I2C_SDA_ADCS: U100.14 (SDA); also elsewhere on the board
I2C_SDA_PMIC: U108.14 (SDA); also elsewhere on the board
I_OUT-A: U108.19 (IN1); also elsewhere on the board
I_OUT-B: U108.5 (IN7); also elsewhere on the board
PHOTODIODE: U100.18 (IN0); also elsewhere on the board
PV_I-A: U108.18 (IN0); also elsewhere on the board
PV_I-B: U108.4 (IN6); also elsewhere on the board
PV_V-A: R142.1; also elsewhere on the board
PV_V-A_JUMP: R142.2, RN101.2 (B1)
PV_V-B: RN100.2 (B1); also elsewhere on the board
PV_V_SENSE-A: RN101.3 (B2), RN101.4 (A2), U108.2 (IN4)
PV_V_SENSE-B: RN100.3 (B2), RN100.4 (A2), U108.3 (IN5)
TEMP-0: U100.19 (IN1); also elsewhere on the board
TEMP-1: U100.20 (IN2); also elsewhere on the board
TEMP-2: U100.1 (IN3); also elsewhere on the board
TEMP-3: U100.2 (IN4); also elsewhere on the board
TEMP-4: U100.3 (IN5); also elsewhere on the board
TEMP-5: U100.4 (IN6); also elsewhere on the board
TEMP-6: U100.5 (IN7); also elsewhere on the board
TEMP_MPPT-A: R139.1, U108.20 (IN2); also elsewhere on the board
TEMP_MPPT-B: R140.1, U108.1 (IN3); also elsewhere on the board

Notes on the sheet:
Variant:
<3C2
<3C2>
CAD note: Decoupling
<3C5>
<3C5
3A5>
CAD note: Decoupling
3A1>
2A1>
2C1>
2C5>
2A3>
2C3>
2A5>

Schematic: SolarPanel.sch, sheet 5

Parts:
C1, C2, C3, C4, C113, C121: 100nF 10%; 1608
H1, H2, H3, H4, H5, H6: M3; MOUNTING_HOLE-3.3
LOGO1: SIGNATUREHENDRIK; SIGN-HENDRIK
LOGO100: Satellite 16mm; CIS-SATELLITE-16
R1, R2, R9, R10, R120, R125: 0Ω <20mΩ; 1608

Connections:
CHASSIS: C1.1, C2.1, C3.1, C4.1, C113.1, C121.1, H1.1, H1.V1, H1.V2, H1.V3, H1.V4, H1.V5, H1.V6, H1.V7, H1.V8, H1.V9, H1.V10, H2.1, H2.V1, H2.V2, H2.V3, H2.V4, H2.V5, H2.V6, H2.V7, H2.V8, H2.V9, H2.V10, H3.1, H3.V1, H3.V2, H3.V3, H3.V4, H3.V5, H3.V6, H3.V7, H3.V8, H3.V9, H3.V10, H4.1, H4.V1, H4.V2, H4.V3, H4.V4, H4.V5, H4.V6, H4.V7, H4.V8, H4.V9, H4.V10, H5.1, H5.V1, H5.V2, H5.V3, H5.V4, H5.V5, H5.V6, H5.V7, H5.V8, H5.V9, H5.V10, H6.1, H6.V1, H6.V2, H6.V3, H6.V4, H6.V5, H6.V6, H6.V7, H6.V8, H6.V9, H6.V10, R1.2, R2.2, R9.2, R10.2, R120.2, R125.2
PGND: C1.2, C2.2, C3.2, C4.2, C113.2, C121.2, R1.1, R2.1, R9.1, R10.1, R120.1, R125.1; also elsewhere on the board

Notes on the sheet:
Variant:
PV-A
PV-B
EPS
ADCS
